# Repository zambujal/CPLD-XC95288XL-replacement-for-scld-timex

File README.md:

# Timex SCLD CPLD Replacement (TC2068)
Target device: Xilinx XC95288XL CPLD

A fully working CPLD replacement for the Timex SCLD — validated on real hardware.

✔ Timing fixes
✔ CMOS Z84 compatible
✔ NMOS Z80 compatible
✔ Tested on real hardware

> This is not just a simulation model — this version works on real hardware.
---
### ERRATA: 
# ERRATA - scld_devboard.vhd

## Output Pin High Impedance - Code Bug

### Problem

The `OE` signal is hardwired to `'1'`, which means the condition:

```vhdl
SIGNAL <= SIGNAL_o_s WHEN OE='1' else 'Z';
```

**never** produces high impedance on any output pin. This is a **code bug**, not a Xilinx hardware limitation.

The XC95288XL correctly implements tristate output buffers (OBUFT) when the condition actually varies — as demonstrated by the `CPUCLK` fix, where using `CPUCLK_o_s='0'` as the condition produces true tristate behaviour.

### Consequence

All output pins remain **push-pull at 3.3V**. Pull-up resistors placed on these output pins have no effect on the HIGH level, since the CPLD actively drives 3.3V. The output will never float to allow an external pull-up to reach 5V.

Pull-ups are only effective where true tristate occurs or on input/bidirectional pins.

### Signal Status

| Signal | Status | Notes |
|--------|--------|-------|
| `CPUCLK` | ✅ Fixed | Condition changed to `CPUCLK_o_s='0'` — true tristate. Use 1kΩ pull-up to 5V (max IOL = 8mA per datasheet). Required for CMOS Z80 compatibility. |
| `TPOUT` | ✅ Fixed | External audio buffer added. |
| `INT` | ✅ Fixed | Open-drain via `'0'/'1'` — correct behaviour, no pull-up to `'Z'` needed. |
| `D`, `MA` | ✅ OK | Bidirectional `inout` — tristate works correctly. |
| `KB` | ✅ OK | Input only — 10kΩ pull-ups correct and required. |
| All other outputs | ⚠️ Push-pull 3.3V | Functional for 5V TTL/CMOS receivers (VIH min = 2.0V). No external buffer needed unless 5V level is required. |

### What Works Despite the Bug

The 3.3V push-pull output is sufficient for most 5V TTL and CMOS receivers (VIH min = 2.0V). The system works correctly with an NMOS Z80. For CMOS Z80, the CPUCLK requires a higher voltage level — fixed with the true tristate + pull-up solution above.

### TODO

- `CPUCLKB` — may benefit from external buffer if CMOS Z80 is used.
- Review and fix the `OE` condition across all output assignments, replacing with signal-specific conditions where true tristate is required.

### Kicad final Beta PCB

My last iteration of the PCB (work in progress...maybe). You might use 10uF on both rails 5v and 3.2v ... I really don't know why I changed from two caps at same value 10 uF, 10 uF is great for the two big caps... don't used electrolitic though "space"... I had to use smaller stuff, but in the end I guess ...I could had used bigger stuff to be easier to solder.

---

## 🎥 Demo (Real Hardware)

> ✔ Proof of real hardware operation — not just simulation

### CPLD Replacement Running (Timex 2048 "Timmy")

https://www.youtube.com/watch?v=t5ia4-bkabo

---

### CPLD Replacement Running (Timex 2068)

https://www.youtube.com/watch?v=evhCbX4_XCQ

---

## 📸 Hardware & Debug

> Real hardware validation using logic analysis and live system testing.

### Logic Analyzer (Timing Validation)

Captured signals used to debug and align timing (MREQ, RAS, CAS, multiplexing).

---

### Timex 2048 ("Timmy") Running with Guzman Logic Analyzer

System running with CPLD-based SCLD replacement, monitored using a Guzman logic analyzer.

---

### Timex 2048 Test System ("Timmy")

Initial test platform where the CPLD implementation was first validated.

---

## 🔌 Hardware Integration Details

The CPLD board was designed to interface with the original Timex hardware using a practical and non-invasive approach.

> ⚠️ No permanent modification to the original system is required (after socket installation).

---

### CPLD Prototype (Hand-Assembled)

Hand-assembled CPLD final prototype (beta version) .

---

### Development Setup (Debug & Measurement)

Temporary wiring and probe points were used during development to access internal signals for measurement and debugging.

These connections were used to:

* Probe critical signals (MREQ, RAS, CAS, etc.)
* Validate timing behaviour
* Debug hardware interactions

⚠️ Note:
Signal artifacts such as spikes/noise observed during this stage were related to the measurement setup, not the final design.

---

### Final Hardware Integration

Final CPLD implementation using right-angle (90°) pin headers.

---

### 90° Pin Integration Technique (Final Design)

Right-angle (90°) pin headers are used as part of the final design to interface the CPLD board with the installed PLCC socket.

This provides:

* Correct alignment with the socket
* Reliable electrical connections
* Mechanical stability
* Easy installation and removal

---

### PLCC Socket Adaptation

The original SCLD is soldered directly to the motherboard in Timex machines.

For this project, a PLCC socket was installed to allow easy testing and replacement without repeatedly soldering components.

This enables:

* Safe insertion and removal of the CPLD board
* Faster development iterations
* Reduced risk of damage to the motherboard

---

## ⚡ Quick Start

1. Program the CPLD with `scld_devboard.jed`
2. Insert into the installed PLCC socket
3. Power on

Done.

---

## 🧠 Overview

This project implements the Timex TC2068 SCLD using a CPLD.

Used in:

* Timex Computer 2048
* Timex Computer 2068

The SCLD is responsible for:

* Memory paging
* Video timing
* Bus arbitration
* DRAM access

---

## 🔧 What was fixed / improved

The original implementation worked on the Timex 2048 with some limitations and was implemented on a smaller CPLD.

However, it was incomplete and did not correctly support key features required for full Timex 2068 compatibility.

This implementation focuses on correct behaviour on real hardware and full system compatibility.

Key improvements include:

- Proper support for Timex 2068 memory paging  
- Implementation of missing I/O behaviour (`IN FF`, `IN F4`)  
- Correct handling of bank switching and EXROM behaviour  
- Timing fixes for reliable operation with both NMOS and CMOS Z80 CPUs  
- Improved stability and DRAM access behaviour  
- Full validation on real hardware (not just simulation)  
---

## 🧪 Development Process

* Started from original VHDL implementation
* Observed incorrect behaviour on real hardware
* Analysed signals using a logic analyzer
* Adjusted timing and internal logic
* Tested with multiple Z80 variants (NMOS / CMOS)
* Validated behaviour against real systems

---

## 🧪 Development Approach

The project evolved through direct hardware testing rather than strict schematic-first design.

Key fixes were implemented and validated directly on the PCB.

---

## 🧰 Hardware

### Final PCB

`Hardware/PCB/Beta/`

Final PCB design used for the working CPLD-based SCLD replacement.

---

### Prototype PCB

`Hardware/PCB/prototype`

Early prototype used during development and testing.

---

### Prototype Schematic

`Hardware/Schematics`

⚠️ Note:
This schematic corresponds to the prototype stage and may differ from the final PCB.

---

## 💾 Firmware

### Prebuilt

`firmware/jed`

* `scld_devboard.jed` → ready to program

---

### Source Code

`firmware/src/`

* VHDL implementation of the SCLD

---

### Constraints

`firmware/constraints/`

* UCF file defining CPLD pin mapping

---

### Xilinx Project

`firmware/xilinx/full_project/`

Full Xilinx ISE project used during development.

⚠️ Note:
Includes generated files (`remote/`, logs, etc.) to preserve the working environment.

Rebuilding is optional — the `.jed` file is sufficient.

---

## 🔍 Validation

Validated against real hardware:

* Video output behaviour
* Memory timing
* System stability
* CPU interaction timing

---

## 🙏 Credits

Based on work from:

- Load ZX Spectrum Museum  
- Álvaro Lopes  
- Paulo Cortesão  

Support:
- João Diogo 
- Hugo Pinto
- Marco Pais
- Inácio Santos
- Fernando

---

### 🧪 Technical Support & Testing

Special thanks to Rui Ribeiro:

- Provided  ROMs used for validation  
- Helped verify behaviour against real systems  
- Shared knowledge of Timex hardware and timing and the weird timex 2068 paging...

---

### 🧠 Implementation (VHDL, Hardware & PCB Design)

- António Vítor  

Complete implementation and validation:

- VHDL development and debugging  
- Timing fixes (MREQ, RAS/CAS, multiplexing)  
- Hardware design and integration  
- PCB design using KiCad  
- CPLD implementation and testing  
- Real hardware validation  

This includes both the logic implementation and the full hardware solution.

---

## 📜 License

Creative Commons Attribution-ShareAlike 4.0 International License

https://creativecommons.org/licenses/by-sa/4.0/

---

## ⚖️ Trademarks

TIMEX is a trademark of TIMEX GROUP USA, INC

The authors are not affiliated with or endorsed by the trademark holders.

Xilinx is a registered trademark of Xilinx, Inc.

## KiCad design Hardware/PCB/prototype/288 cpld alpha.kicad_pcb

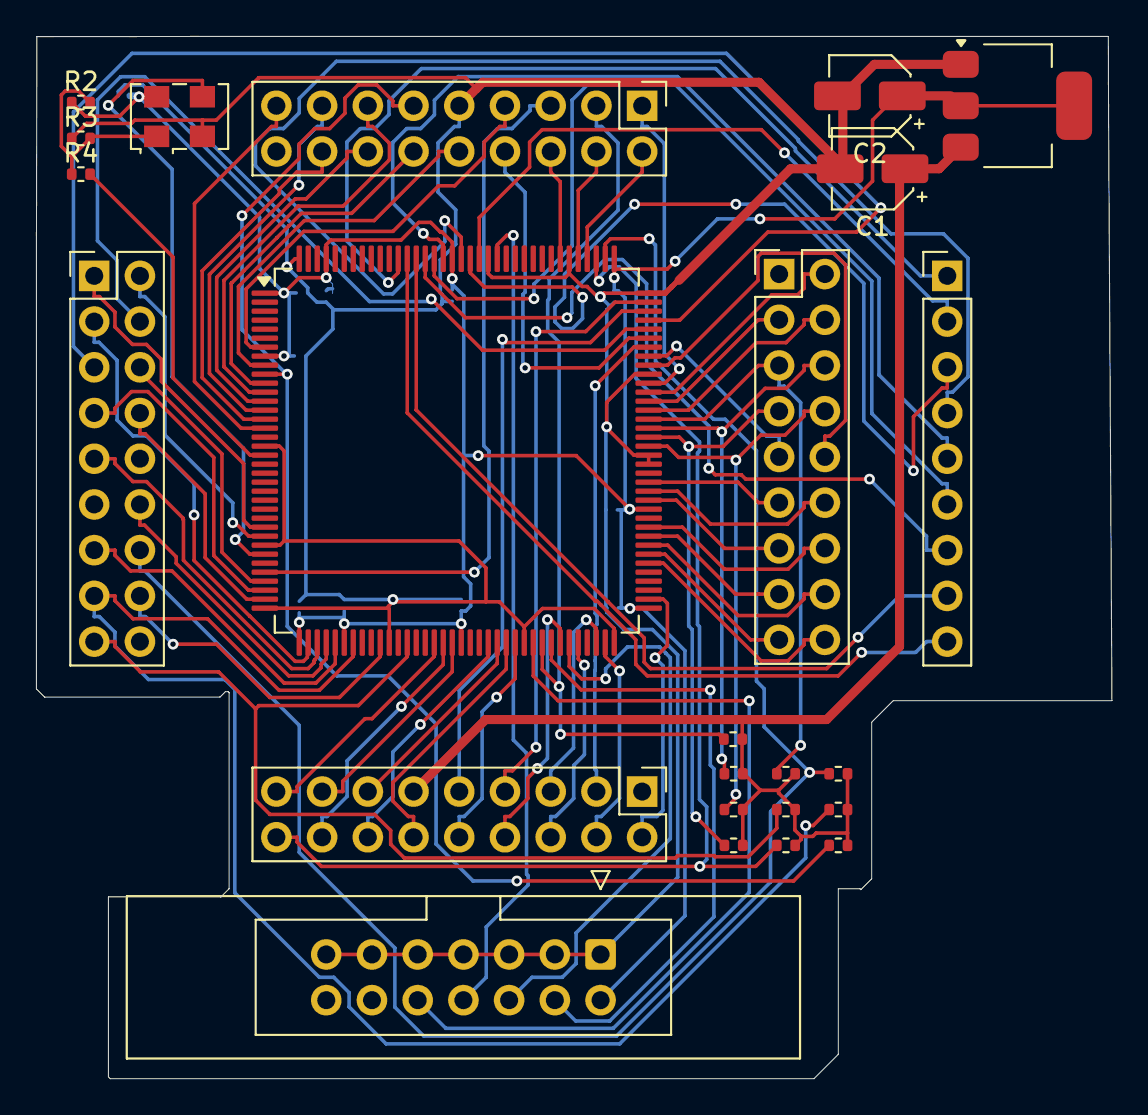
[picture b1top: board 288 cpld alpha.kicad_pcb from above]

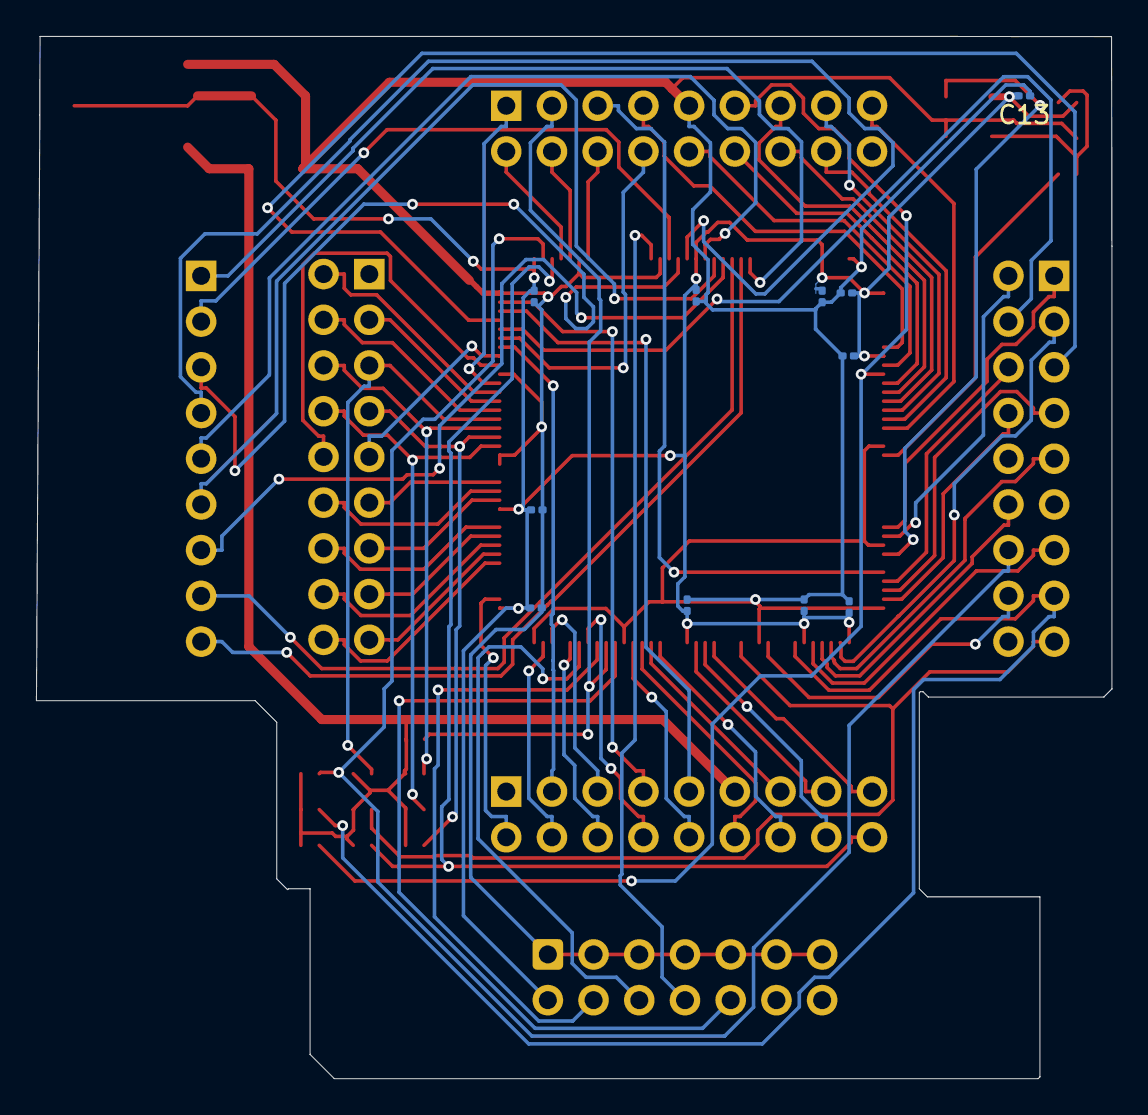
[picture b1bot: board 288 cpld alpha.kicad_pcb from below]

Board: 2 copper layers, 59.8 x 57.9 mm, 35 parts (11 on the bottom side), 83 nets.

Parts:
C1, C2: C_Small; CP_Elec_4x5.3
C3, C4, C5, C6, C7, C8, C9, C10, C11, C12, C13: C_Small; C_0201_0603Metric
J1, J3, J4, J5: Conn_02x09_Counter_Clockwise; PinHeader_2x09_P2.54mm_Vertical
J2: Conn_01x09_Pin; PinHeader_1x09_P2.54mm_Vertical
J6: JTAG-10; IDC-Header_2x07_P2.54mm_Latch_Vertical
R1, R2, R3, R4, R25, R26, R27, R28, R29, R30, R31, R32, R33: R; R_0402_1005Metric
U1: LM1117DT-3.3; SOT-223-3_TabPin2
U2: XCR3256-TQ144; TQFP-144_20x20mm_P0.5mm
X2: ASE-14MHz; Oscillator_SMD_EuroQuartz_XO53-4Pin_5.0x3.2mm

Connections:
+3.3V: C2.1, C3.2, C4.2, C5.2, C6.2, C7.2, C8.2, C9.2, C10.2, C11.2, C12.2, C13.2, J6.2 (vcc), R2.1, U1.2 (VO), U2.1 (VCCIO), U2.8 (VCCINT), U2.37 (VCCIO), U2.42 (VCCINT), U2.55 (VCCIO), U2.73 (VCCIO), U2.84 (VCCINT), U2.109 (VCCIO), U2.127 (VCCIO), U2.141 (VCCINT), X2.4 (Vdd)
+5V: C1.1, J4.11, R1.2, R25.2, R26.2, R27.2, R28.2, R29.2, R30.2, R31.2, R32.2, R33.2, U1.3 (VI)
/A0: J5.10, U2.100 (I/O_geral)
/A1: J5.11, U2.87 (I/O_geral)
/A2: J5.13, U2.85 (I/O_geral)
/A3: J5.9, U2.101 (I/O_geral)
/A4: J5.12, U2.86 (I/O_geral)
/A5: J4.2, U2.74 (I/O_geral)
/A6: J5.15, U2.81 (I/O_geral)
/A7: J5.17, U2.79 (I/O_geral)
/A7RB: J3.14, U2.13 (I/O_geral)
/A13: J1.1, U2.27 (I/O_geral)
/A14: J1.4, U2.104 (I/O_geral)
/A15: J3.16, U2.15 (I/O_geral)
/AYCLOCK: J1.3, U2.38 (Global_Clock_3)
/B: J1.15, R32.1, U2.43 (I/O_geral)
/BC1: J5.4, U2.95 (I/O_geral)
/BDIR: J5.16, U2.80 (I/O_geral)
/BE: J1.8, U2.35 (I/O_geral)
/BRIGHT: J3.11, R33.1, U2.10 (I/O_geral)
/CAS: J3.13, U2.12 (I/O_geral)
/CAS1: J4.16, U2.53 (I/O_geral)
/CAS2: J4.14, U2.58 (I/O_geral)
/CPUCLK: J3.5, U2.32 (Global_Clock_2)
/CPUCLKB: J5.14, U2.82 (I/O_geral)
/CSYNC: J5.2, U2.97 (I/O_geral)
/D0: J3.2, U2.112 (I/O_geral)
/D1: J4.3, U2.102 (I/O_geral)
/D2: J4.4, U2.71 (I/O_geral)
/D3: J3.4, U2.113 (I/O_geral)
/D4: J3.8, U2.103 (I/O_geral)
/D5: J3.10, U2.9 (I/O_geral)
/D6: J4.6, U2.68 (I/O_geral)
/D7: J4.10, U2.61 (I/O_geral)
/EXROM: J1.13, U2.41 (I/O_geral)
/G: J1.14, R31.1, U2.110 (I/O_geral)
/INT: J1.7, U2.34 (I/O_geral)
/IORQ: J1.6, U2.33 (I/O_geral)
/KB0: J5.6, R25.1, U2.93 (I/O_geral)
/KB1: J5.8, R26.1, U2.91 (I/O_geral)
/KB2: J5.7, R27.1, U2.92 (I/O_geral)
/KB3: J5.5, R28.1, U2.94 (I/O_geral)
/KB4: J1.17, R29.1, U2.49 (I/O_geral)
/MA0: J4.5, U2.70 (I/O_geral)
/MA1: J4.9, U2.106 (I/O_geral)
/MA2: J4.13, U2.59 (I/O_geral)
/MA3: J4.7, U2.107 (I/O_geral)
/MA4: J3.12, U2.11 (I/O_geral)
/MA5: J3.6, U2.115 (I/O_geral)
/MA6: J3.7, U2.7 (I/O_geral)
/MA7: J4.8, U2.66 (I/O_geral)
/MREQ: J1.5, U2.105 (I/O_geral)
/MUX: J5.3, U2.96 (I/O_geral)
/P5060: J3.17, U2.16 (I/O_geral)
/R: J4.18, R30.1, U2.111 (I/O_geral)
/RAS: J4.17, U2.52 (I/O_geral)
/RD: J3.15, U2.14 (I/O_geral)
/RDN: J5.18, U2.78 (I/O_geral)
/ROMCS: J1.9, U2.39 (I/O_geral)
/ROSCS: J1.12, U2.40 (I/O_geral)
/RSH: J1.2, U2.28 (I/O_geral)
/TCK: J6.6 (TCK), U2.67 (E0/TCK)
/TDI: J6.10 (TDI), U2.63 (J0/TDI)
/TDO: J6.8 (TDO), U2.122 (A2/TDO)
/TMS: J6.4 (TMS), U2.65 (N0/TMS)
/TPIN: J3.1, U2.98 (I/O_geral)
/TPOUT: J3.3, R1.1, U2.64 (I/O_geral)
/TS: J4.15, U2.54 (I/O_geral)
/WE: J4.12, U2.60 (I/O_geral)
/WR: J1.16, U2.46 (I/O_geral)
/p1: J2.3, U2.125 (I/O_geral)
/p2: J2.4, U2.126 (I/O_geral)
/p3: J2.5, U2.128 (I/O_geral)
/p4: J2.6, U2.129 (I/O_geral)
/p5: J2.7, U2.130 (I/O_geral)
/p6: J2.8, U2.131 (I/O_geral)
/p7: J2.9, U2.132 (I/O_geral)
/p8: J2.2, U2.124 (I/O_geral)
/p9: J2.1, U2.133 (I/O_geral)
/xin: U2.30 (Global_Clock_1), X2.3 (OUT)
/xout: R4.2, U2.19 (I/O_geral)
GND: C1.2, C2.2, C3.1, C4.1, C5.1, C6.1, C7.1, C8.1, C9.1, C10.1, C11.1, C12.1, C13.1, J3.9, J6.1 (gnd), J6.3 (gnd), J6.5 (gnd), J6.7 (gnd), J6.9 (gnd), J6.11 (gnd), J6.13 (gnd), R3.1, U1.1 (GND), U2.18 (GND), U2.29 (GND), U2.36 (GND), U2.47 (GND), U2.62 (GND), U2.72 (GND), U2.89 (GND), U2.90 (GND), U2.99 (GND), U2.108 (GND), U2.114 (GND), U2.123 (GND), U2.144 (GND), X2.2 (GND)
unnamed: R2.2, R3.2, R4.1, X2.1 (EN)

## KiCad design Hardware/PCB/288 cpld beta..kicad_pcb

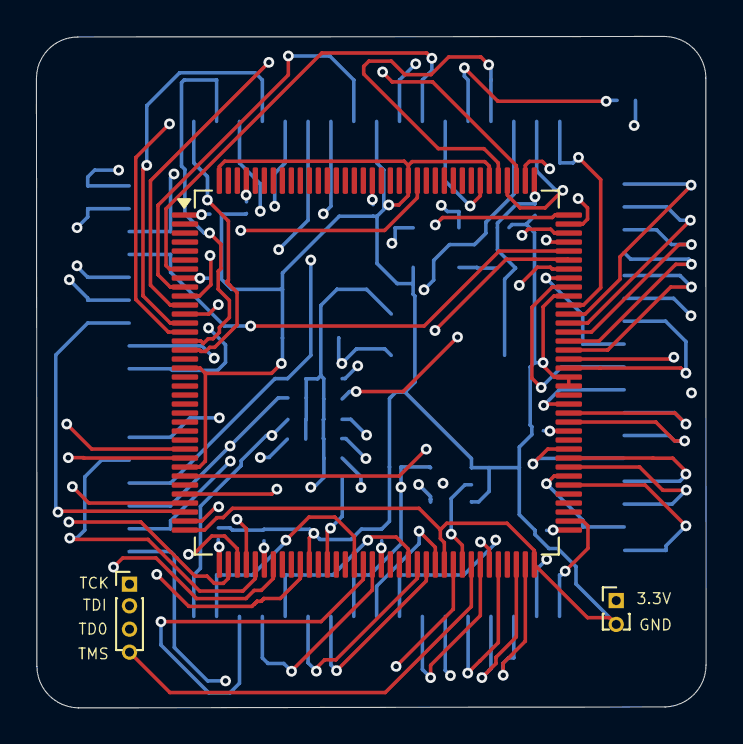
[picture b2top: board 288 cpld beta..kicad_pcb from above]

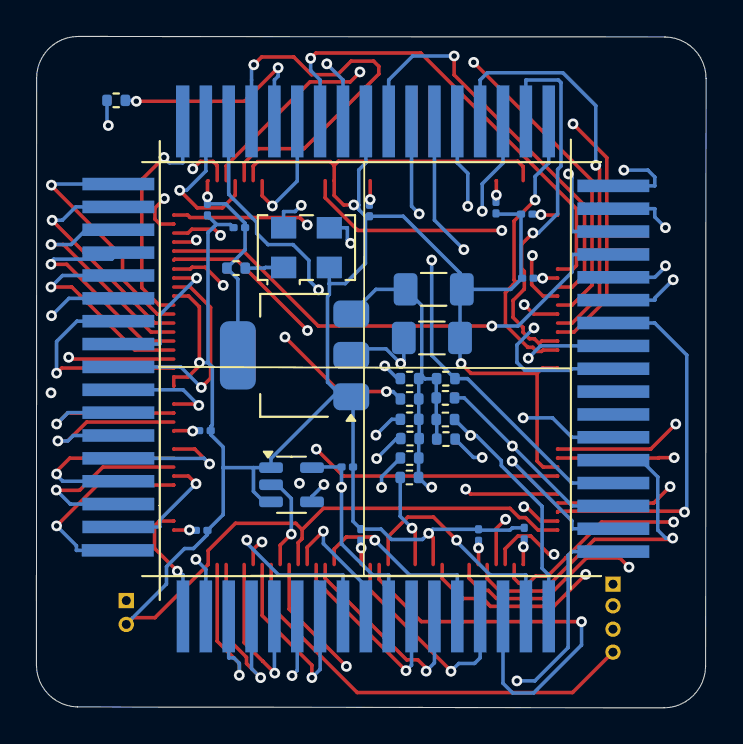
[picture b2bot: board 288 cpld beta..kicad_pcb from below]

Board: 4 copper layers, 37.2 x 37.3 mm, 33 parts (29 on the bottom side), 74 nets.

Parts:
C1, C2: C_Small; C_1206_3216Metric_Pad1.33x1.80mm_HandSolder
C3, C4, C5, C6, C7, C8, C9, C9x, C10, C11, C12, C13: C_Small; C_0201_0603Metric
R1, R2, R25, R26, R27, R28, R29, R30, R31, R32, R33: R; R_0402_1005Metric
R2pullclock: 330; R_0402_1005Metric
REF9: PinHeader_1x04_P1.00mm_Vertical
REF10: PinHeader_1x02_P1.00mm_Vertical
U1: LM1117DT-3.3; SOT-223-3_TabPin2
U2: XCR3256-TQ144; TQFP-144_20x20mm_P0.5mm
U3: SN74LVC1G125DBV; SOT-23-5
X2: ASE-14MHz; Oscillator_SMD_EuroQuartz_XO53-4Pin_5.0x3.2mm
programação: 68 scld; 68_scld (2)

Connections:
+3.3V: C2.1, C3.2, C4.2, C5.2, C6.2, C7.2, C8.2, C9.2, C10.2, C11.2, C12.2, C13.2, R2.1, REF10.1, U1.2 (VO), U2.1 (VCCIO), U2.8 (VCCINT), U2.37 (VCCIO), U2.42 (VCCINT), U2.55 (VCCIO), U2.73 (VCCIO), U2.84 (VCCINT), U2.109 (VCCIO), U2.127 (VCCIO), U2.141 (VCCINT), X2.4 (Vdd)
+5V: C1.1, C9x.2, R1.2, R2pullclock.1, R25.2, R26.2, R27.2, R28.2, R29.2, R30.2, R31.2, R32.2, R33.2, U1.3 (VI), U3.5 (VCC), programação.27
/A0: U2.100 (I/O_geral), programação.9
/A1: U2.87 (I/O_geral), programação.10
/A2: U2.85 (I/O_geral), programação.12
/A3: U2.101 (I/O_geral), programação.8
/A4: U2.86 (I/O_geral), programação.11
/A5: U2.74 (I/O_geral), programação.18
/A6: U2.81 (I/O_geral), programação.14
/A7: U2.79 (I/O_geral), programação.16
/A7RB: U2.13 (I/O_geral), programação.55
/A13: U2.27 (I/O_geral), programação.51
/A14: U2.104 (I/O_geral), programação.48
/A15: U2.15 (I/O_geral), programação.53
/AYCLOCK: U2.38 (Global_Clock_3), programação.49
/B: R32.1, U2.43 (I/O_geral), programação.37
/BC1: U2.95 (I/O_geral), programação.3
/BDIR: U2.80 (I/O_geral), programação.15
/BE: U2.35 (I/O_geral), programação.44
/BRIGHT: R33.1, U2.10 (I/O_geral), programação.58
/CAS: U2.12 (I/O_geral), programação.56
/CAS1: U2.53 (I/O_geral), programação.32
/CAS2: U2.58 (I/O_geral), programação.30
/CPUCLK: R2pullclock.2, U2.32 (Global_Clock_2), programação.64
/CPUCLKB: U2.82 (I/O_geral), programação.13
/CSYNC: U2.97 (I/O_geral), programação.1
/D0: U2.112 (I/O_geral), programação.67
/D1: U2.102 (I/O_geral), programação.19
/D2: U2.71 (I/O_geral), programação.20
/D3: U2.113 (I/O_geral), programação.65
/D4: U2.103 (I/O_geral), programação.61
/D5: U2.9 (I/O_geral), programação.59
/D6: U2.68 (I/O_geral), programação.22
/D7: U2.61 (I/O_geral), programação.26
/EXROM: U2.41 (I/O_geral), programação.39
/G: R31.1, U2.110 (I/O_geral), programação.38
/INT: U2.34 (I/O_geral), programação.45
/IORQ: U2.33 (I/O_geral), programação.46
/KB0: R25.1, U2.93 (I/O_geral), programação.5
/KB1: R26.1, U2.91 (I/O_geral), programação.7
/KB2: R27.1, U2.92 (I/O_geral), programação.6
/KB3: R28.1, U2.94 (I/O_geral), programação.4
/KB4: R29.1, U2.49 (I/O_geral), programação.35
/MA0: U2.70 (I/O_geral), programação.21
/MA1: U2.106 (I/O_geral), programação.25
/MA2: U2.59 (I/O_geral), programação.29
/MA3: U2.107 (I/O_geral), programação.23
/MA4: U2.11 (I/O_geral), programação.57
/MA5: U2.115 (I/O_geral), programação.63
/MA6: U2.7 (I/O_geral), programação.62
/MA7: U2.66 (I/O_geral), programação.24
/MREQ: U2.105 (I/O_geral), programação.47
/MUX: U2.96 (I/O_geral), programação.2
/P5060: U2.16 (I/O_geral), programação.52
/R: R30.1, U2.111 (I/O_geral), programação.34
/RAS: U2.52 (I/O_geral), programação.33
/RD: U2.14 (I/O_geral), programação.54
/RDN: U2.78 (I/O_geral), programação.17
/ROMCS: U2.39 (I/O_geral), programação.43
/ROSCS: U2.40 (I/O_geral), programação.40
/RSH: U2.28 (I/O_geral), programação.50
/TCK: REF9.1, U2.67 (E0/TCK)
/TDI: REF9.2, U2.63 (J0/TDI)
/TDO: REF9.3, U2.122 (A2/TDO)
/TMS: REF9.4, U2.65 (N0/TMS)
/TPIN: U2.98 (I/O_geral), programação.68
/TPOUT: R1.1, U3.4, programação.66
/TS: U2.54 (I/O_geral), programação.31
/WE: U2.60 (I/O_geral), programação.28
/WR: U2.46 (I/O_geral), programação.36
/xin: U2.30 (Global_Clock_1), X2.3 (OUT)
GND: C1.2, C2.2, C3.1, C4.1, C5.1, C6.1, C7.1, C8.1, C9.1, C9x.1, C10.1, C11.1, C12.1, C13.1, REF10.2, U1.1 (GND), U2.18 (GND), U2.29 (GND), U2.36 (GND), U2.47 (GND), U2.62 (GND), U2.72 (GND), U2.89 (GND), U2.90 (GND), U2.99 (GND), U2.108 (GND), U2.114 (GND), U2.123 (GND), U2.144 (GND), U3.1, U3.3 (GND), X2.2 (GND), programação.60
unnamed: R2.2, X2.1 (EN)
tpoutemp: U2.64 (I/O_geral), U3.2

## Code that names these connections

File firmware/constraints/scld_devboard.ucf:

NET	"TPIN" 		LOC="98";
NET	"D<0>" 		LOC="112";
NET	"D<3>" 		LOC="113";
//NET	"CPUCLK"	LOC="4";
NET	"MA<5>"		LOC="115";
NET	"MA<6>"		LOC="7";
NET	"D<4>"		LOC="103";
NET	"D<5>"		LOC="9";
NET	"BRIGHT"	LOC="10";
NET	"MA<4>"		LOC = "11";
NET	"CAS" 		LOC = "12";
NET	"A7RB" 		LOC = "13";
NET	"RD" 		LOC = "14";
NET	"A<15>" 	LOC = "15";
NET	"P5060"		LOC = "16";
//NET	"NOE" 		LOC="18";
NET	"SCLD_CLK"	LOC = "30";
NET	"CPUCLK"	LOC = "32";
NET	"A<13>"		LOC = "27";
NET	"RFSH"		LOC = "28";
NET	"AYCLK"		LOC = "38";
NET	"A<14>"		LOC = "104";
NET	"MREQ"		LOC = "105";
NET	"IORQ"		LOC = "33";
NET	"INT"		LOC = "34";

NET	"BE"		LOC = "35";
NET	"ROMCS"		LOC = "39";
NET	"ROSCS"		LOC = "40";
NET	"EXROM"		LOC = "41";
NET	"G"		LOC = "110";
NET	"B"		LOC = "43";
NET	"WR"		LOC = "46";
NET	"KB<4>"		LOC = "49";

NET	"RAS"		LOC = "52";
NET	"CAS1"		LOC = "53";
NET	"TS"		LOC = "54";
NET	"CAS2"		LOC = "58";
NET	"MA<2>"		LOC = "59";
NET	"MWE"		LOC = "60";
NET	"D<7>"		LOC = "61";

NET	"R"		LOC = "111";
NET	"TPOUT"		LOC = "64";
NET	"MA<1>"		LOC = "106";
NET	"MA<7>"		LOC = "66";
NET	"MA<3>"		LOC = "107";
NET	"D<6>"		LOC = "68";
NET	"MA<0>"		LOC = "70";
NET	"D<2>"		LOC = "71";
NET	"D<1>"		LOC = "102";

NET	"A<5>"		LOC = "74";
NET	"RDN"		LOC = "78";
NET	"A<7>"		LOC = "79";
NET	"BDIR"		LOC = "80";
NET	"A<6>"		LOC = "81";
NET	"CPUCLKB"	LOC = "82";
NET	"A<2>"		LOC = "85";
NET	"A<4>"		LOC = "86";

NET	"A<1>"		LOC = "87";
NET	"A<0>"		LOC = "100";
NET	"A<3>"		LOC = "101";
NET	"KB<1>"		LOC = "91";
NET	"KB<2>"		LOC = "92";
NET	"KB<0>"		LOC = "93";
NET	"KB<3>"		LOC = "94";
NET	"BC1"		LOC = "95";
NET	"MUX"		LOC = "96";
NET	"CSYNC"		LOC = "97";

NET 	"SCLD_CLK" 	TNM_NET = SCLD_CLK;
NET   "EPROM_CE" LOC = "132";
TIMESPEC TS_SCLD_CLK = PERIOD "SCLD_CLK" 14 MHz HIGH 50%;

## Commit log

2025-08-03 Add files via upload
    flash para programar o xilinx...
    cpld para o timmy...
2026-03-04 Add files via upload
    functional cpld code for the 288 detected in FF and F4 not implemented... ok now do the 2068 boot
2026-04-24 Revise README for clarity and additional information
    Updated the README to provide a clearer overview, added sections for credits and license, and detailed improvements made to the CPLD implementation.
2026-04-24 Create pcb
2026-04-24 Create files
2026-04-24 Add files via upload
    beta mas most likely final
2026-04-24 Add new test file in Beta directory
2026-04-24 Create file
2026-04-24 Create test
2026-04-24 Add hardware validation details to README
    Added hardware validation section with images and descriptions.
2026-04-24 Refactor README for better structure and readability
    Updated README.md to improve formatting and clarity.
2026-04-24 Remove duplicate Hardware & Debug section header
2026-04-24 Revise README for clarity and additional content
    Updated README to enhance project description, added demo and validation sections, and improved formatting.
2026-04-24 Update image in README for working setup
2026-04-24 Update CPLD Replacement reference to Timex 2068
2026-04-24 Rename CPLD Replacement and add new video link
    Updated the demo section to reflect the correct name and added a new video link for the Timex 2068.
2026-04-24 Remove duplicate hardware reference from README
    Removed duplicate original hardware reference link from README.
2026-04-24 Update section title for Timex 2068 hardware
2026-04-24 Update README with Timex 2048 references and corrections
2026-04-24 Update compatibility information in README
2026-04-24 Rename Timex 2048 Test System to Timex 2048 Test System AKA timmy
2026-04-24 Enhance README with hardware integration and debug details
    Expanded hardware integration details and added sections on CPLD prototype, development setup, final PCB solution, PLCC socket compatibility, and debugging techniques.
2026-04-24 Revise README for hardware integration and CPLD details
    Updated hardware integration details and clarified CPLD prototype information.
2026-04-24 Revise CPLD prototype description and add image
    Updated description of the CPLD prototype and added a new image.
2026-04-24 Correct directory paths in README.md
    Updated directory paths in README for hardware and firmware sections.
2026-04-24 Add target device information to README
2026-04-24 Specify target device in README
    Added target device information for clarity.
2026-04-24 Enhance README with detailed implementation improvements
    Updated README to clarify improvements and fixes for Timex 2068 compatibility.
2026-04-25 Add Kicad final Beta PCB section to README
    Added section for Kicad final Beta PCB with image.
2026-04-26 Update image in README for Kicad PCB
2026-04-26 Update image format from JPG to PNG in README
2026-04-26 Update PCB notes in README
    Clarified PCB notes regarding capacitor usage.
2026-04-26 Update PCB description for clarity
    Clarified reasoning for capacitor selection in PCB description.
2026-04-26 Update PCB description in README.md
    Expanded explanation about PCB capacitor choices and soldering.
2026-05-09 Documented errata and output pin issues in README
    Added errata section detailing a code bug with the OE signal and its consequences on output pin behavior. Included signal status and what works despite the bug.
